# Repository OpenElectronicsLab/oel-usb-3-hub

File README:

Open Electronics Lab USB 3 hub
Copyright (C) 2022 Eric Herman
SPDX-License-Identifier: CERN-OHL-S-2.0+

This is a work in progress

License
-------
You may redistribute and modify this source and make products using it
under the terms of the CERN-OHL-S v2 (CERN Open Hardware Licence Version
2 - Strongly Reciprocal, https://ohwr.org/cern_ohl_s_v2.txt), or any
later version.

This source is distributed WITHOUT ANY EXPRESS OR IMPLIED WARRANTY,
INCLUDING OF MERCHANTABILITY, SATISFACTORY QUALITY AND FITNESS FOR A
PARTICULAR PURPOSE. Please see the CERN-OHL-S v2 for applicable
conditions.

Source location: https://github.com/OpenElectronicsLab/oel-usb-3-hub

As per CERN-OHL-S v2 section 4, should You produce hardware based on
this source, You must where practicable maintain the Source Location
visible on the external case of the Gizmo or other products you make
using this source.

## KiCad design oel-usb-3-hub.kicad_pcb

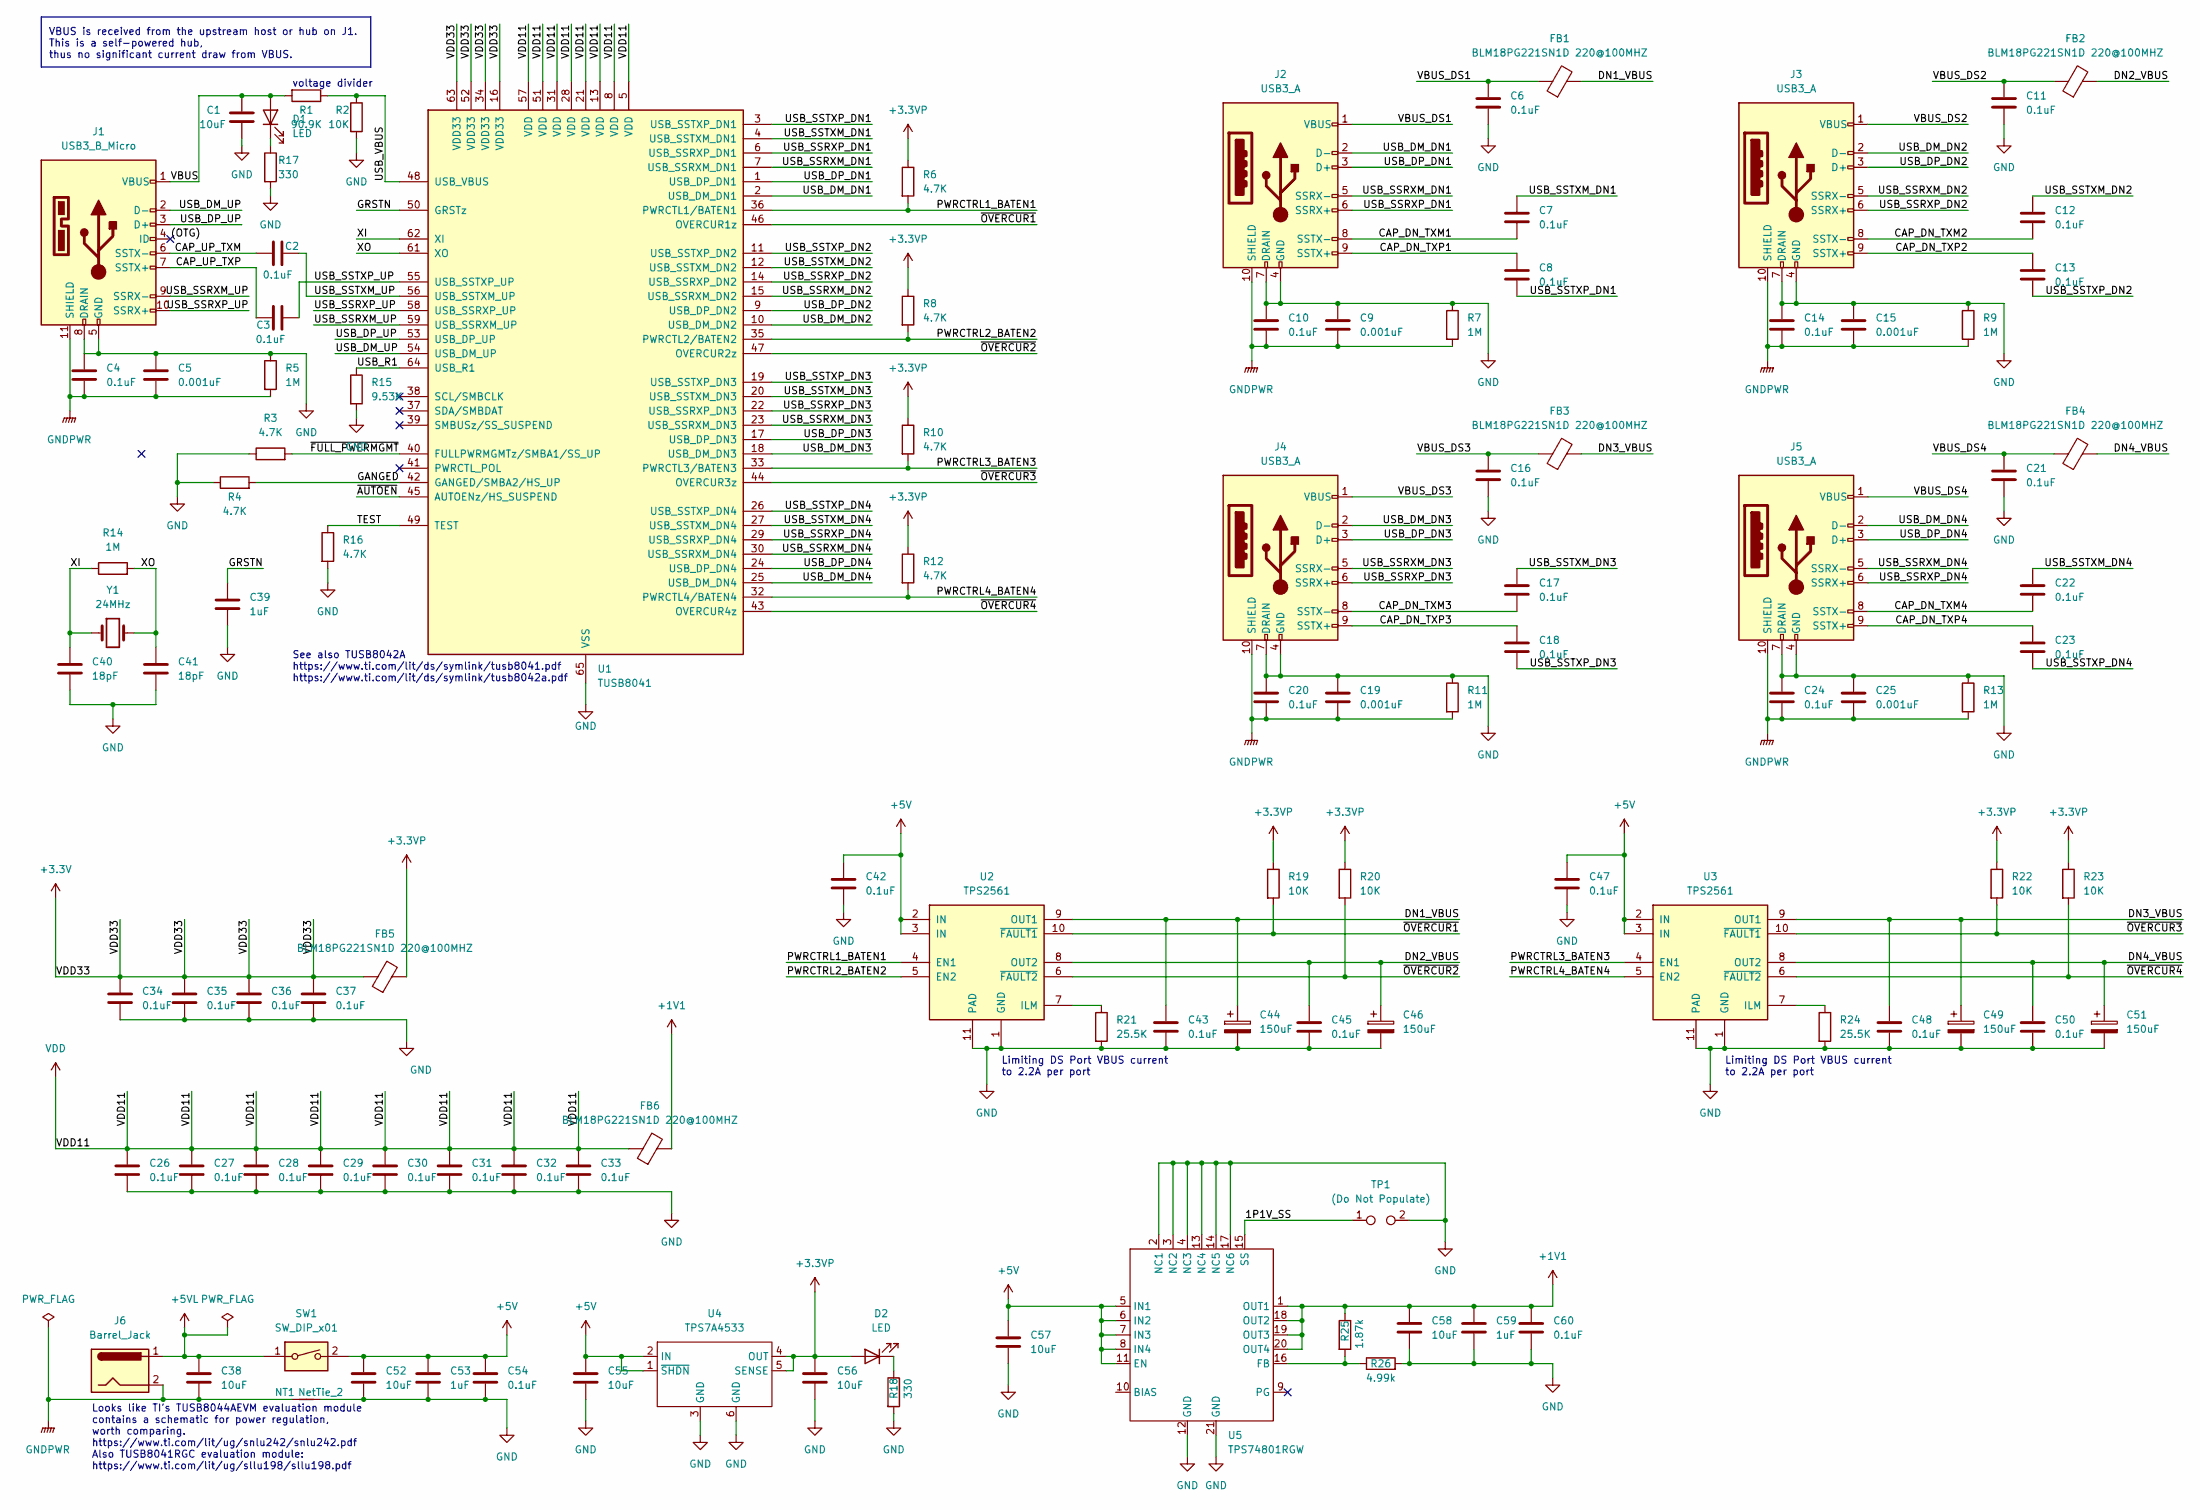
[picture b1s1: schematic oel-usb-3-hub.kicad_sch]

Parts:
C1, C38, C52, C55, C56, C57, C58: 10uF; C_0603_1608Metric_Pad1.08x0.95mm_HandSolder
C2, C3, C4, C6, C7, C8, C10, C11, C12, C13, C14, C16, C17, C18, C20, C21, C22, C23, C24, C26, C27, C28, C29, C30, C31, C32, C33, C34, C35, C36, C37, C42, C43, C45, C47, C48, C50, C54, C60: 0.1uF; C_0603_1608Metric_Pad1.08x0.95mm_HandSolder
C5, C9, C15, C19, C25: 0.001uF; C_0603_1608Metric_Pad1.08x0.95mm_HandSolder
C39, C53, C59: 1uF; C_0603_1608Metric_Pad1.08x0.95mm_HandSolder
C40, C41: 18pF; C_0603_1608Metric_Pad1.08x0.95mm_HandSolder
C44, C46, C49, C51: 150uF; C_0603_1608Metric_Pad1.08x0.95mm_HandSolder
D1, D2: LED; D_0603_1608Metric_Pad1.05x0.95mm_HandSolder
FB1, FB2, FB3, FB4, FB5, FB6: BLM18PG221SN1D 220@100MHZ; R_0603_1608Metric_Pad0.98x0.95mm_HandSolder
J1: USB3_B_Micro; USB3_Micro-B_Connfly_DS1104-01
J2, J3, J4, J5: USB3_A; USB3_A_Molex_48393-001
J6: Barrel_Jack; BarrelJack_Horizontal
NT1: NetTie_2; NetTie-2_SMD_Pad2.0mm
R1: 90.9K; R_0603_1608Metric_Pad0.98x0.95mm_HandSolder
R2, R19, R20, R22, R23: 10K; R_0603_1608Metric_Pad0.98x0.95mm_HandSolder
R3, R4, R6, R8, R10, R12, R16: 4.7K; R_0603_1608Metric_Pad0.98x0.95mm_HandSolder
R5, R7, R9, R11, R13, R14: 1M; R_0603_1608Metric_Pad0.98x0.95mm_HandSolder
R15: 9.53K; R_0603_1608Metric_Pad0.98x0.95mm_HandSolder
R17, R18: 330; R_0603_1608Metric_Pad0.98x0.95mm_HandSolder
R21, R24: 25.5K; R_0603_1608Metric_Pad0.98x0.95mm_HandSolder
R25: 1.87k; R_0603_1608Metric_Pad0.98x0.95mm_HandSolder
R26: 4.99k; R_0603_1608Metric_Pad0.98x0.95mm_HandSolder
SW1: SW_DIP_x01; SW_DIP_SPSTx01_Slide_6.7x4.1mm_W7.62mm_P2.54mm_LowProfile
TP1: (Do Not Populate); R_0603_1608Metric_Pad0.98x0.95mm_HandSolder
U1: TUSB8041; QFN-64-1EP_9x9mm_P0.5mm_EP6x6mm_ThermalVias
U2, U3: TPS2561; VSON-10-1EP_3x3mm_P0.5mm_EP1.65x2.4mm_ThermalVias
U4: TPS7A4533; SOT-223-6_TabPin3
U5: TPS74801RGW; Texas_S-PVQFN-N20_EP3.15x3.15mm_ThermalVias
Y1: 24MHz; Crystal_HC49-U_Vertical

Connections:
+1V1: C58.1, C59.1, C60.1, FB6.2, R25.1, U5.1 (OUT1), U5.18 (OUT2), U5.19 (OUT3), U5.20 (OUT4)
+3.3V: C34.1, C35.1, C36.1, C37.1, FB5.1, U1.16 (VDD33), U1.34 (VDD33), U1.52 (VDD33), U1.63 (VDD33)
+3.3VP: C56.1, D2.2 (A), FB5.2, R6.1, R8.1, R10.1, R12.1, R19.1, R20.1, R22.1, R23.1, U4.4 (OUT), U4.5 (SENSE)
+5V: C42.1, C47.1, C52.1, C53.1, C54.1, C55.1, C57.1, SW1.2, U2.2 (IN), U2.3 (IN), U3.2 (IN), U3.3 (IN), U4.1 (~SHDN), U4.2 (IN), U5.5 (IN1), U5.6 (IN2), U5.7 (IN3), U5.8 (IN4), U5.11 (EN)
+5VL: C38.1, J6.1, SW1.1
/1P1V_SS: TP1.1, U5.15 (SS)
/(OTG): J1.4 (ID)
/CAP_DN_TXM1: C7.2, J2.8 (SSTX-)
/CAP_DN_TXM2: C12.2, J3.8 (SSTX-)
/CAP_DN_TXM3: C17.2, J4.8 (SSTX-)
/CAP_DN_TXM4: C22.2, J5.8 (SSTX-)
/CAP_DN_TXP1: C8.1, J2.9 (SSTX+)
/CAP_DN_TXP2: C13.1, J3.9 (SSTX+)
/CAP_DN_TXP3: C18.1, J4.9 (SSTX+)
/CAP_DN_TXP4: C23.1, J5.9 (SSTX+)
/CAP_UP_TXM: C2.1, J1.6 (SSTX-)
/CAP_UP_TXP: C3.1, J1.7 (SSTX+)
/DN1_VBUS: C43.1, C44.1, FB1.2, U2.9 (OUT1)
/DN2_VBUS: C45.1, C46.1, FB2.2, U2.8 (OUT2)
/DN3_VBUS: C48.1, C49.1, FB3.2, U3.9 (OUT1)
/DN4_VBUS: C50.1, C51.1, FB4.2, U3.8 (OUT2)
/GANGED: R4.2, U1.42 (GANGED/SMBA2/HS_UP)
/GRSTN: C39.1, U1.50 (GRSTz)
/PWRCTRL1_BATEN1: R6.2, U1.36 (PWRCTL1/BATEN1), U2.4 (EN1)
/PWRCTRL2_BATEN2: R8.2, U1.35 (PWRCTL2/BATEN2), U2.5 (EN2)
/PWRCTRL3_BATEN3: R10.2, U1.33 (PWRCTL3/BATEN3), U3.4 (EN1)
/PWRCTRL4_BATEN4: R12.2, U1.32 (PWRCTL4/BATEN4), U3.5 (EN2)
/TEST: R16.1, U1.49 (TEST)
/USB_DM_DN1: J2.2 (D-), U1.2 (USB_DM_DN1)
/USB_DM_DN2: J3.2 (D-), U1.10 (USB_DM_DN2)
/USB_DM_DN3: J4.2 (D-), U1.18 (USB_DM_DN3)
/USB_DM_DN4: J5.2 (D-), U1.25 (USB_DM_DN4)
/USB_DM_UP: J1.2 (D-), U1.54 (USB_DM_UP)
/USB_DP_DN1: J2.3 (D+), U1.1 (USB_DP_DN1)
/USB_DP_DN2: J3.3 (D+), U1.9 (USB_DP_DN2)
/USB_DP_DN3: J4.3 (D+), U1.17 (USB_DP_DN3)
/USB_DP_DN4: J5.3 (D+), U1.24 (USB_DP_DN4)
/USB_DP_UP: J1.3 (D+), U1.53 (USB_DP_UP)
/USB_R1: R15.1, U1.64 (USB_R1)
/USB_SSRXM_DN1: J2.5 (SSRX-), U1.7 (USB_SSRXM_DN1)
/USB_SSRXM_DN2: J3.5 (SSRX-), U1.15 (USB_SSRXM_DN2)
/USB_SSRXM_DN3: J4.5 (SSRX-), U1.23 (USB_SSRXM_DN3)
/USB_SSRXM_DN4: J5.5 (SSRX-), U1.30 (USB_SSRXM_DN4)
/USB_SSRXM_UP: J1.9 (SSRX-), U1.59 (USB_SSRXM_UP)
/USB_SSRXP_DN1: J2.6 (SSRX+), U1.6 (USB_SSRXP_DN1)
/USB_SSRXP_DN2: J3.6 (SSRX+), U1.14 (USB_SSRXP_DN2)
/USB_SSRXP_DN3: J4.6 (SSRX+), U1.22 (USB_SSRXP_DN3)
/USB_SSRXP_DN4: J5.6 (SSRX+), U1.29 (USB_SSRXP_DN4)
/USB_SSRXP_UP: J1.10 (SSRX+), U1.58 (USB_SSRXP_UP)
/USB_SSTXM_DN1: C7.1, U1.4 (USB_SSTXM_DN1)
/USB_SSTXM_DN2: C12.1, U1.12 (USB_SSTXM_DN2)
/USB_SSTXM_DN3: C17.1, U1.20 (USB_SSTXM_DN3)
/USB_SSTXM_DN4: C22.1, U1.27 (USB_SSTXM_DN4)
/USB_SSTXM_UP: C2.2, U1.56 (USB_SSTXM_UP)
/USB_SSTXP_DN1: C8.2, U1.3 (USB_SSTXP_DN1)
/USB_SSTXP_DN2: C13.2, U1.11 (USB_SSTXP_DN2)
/USB_SSTXP_DN3: C18.2, U1.19 (USB_SSTXP_DN3)
/USB_SSTXP_DN4: C23.2, U1.26 (USB_SSTXP_DN4)
/USB_SSTXP_UP: C3.2, U1.55 (USB_SSTXP_UP)
/USB_VBUS: R1.1, R2.1, U1.48 (USB_VBUS)
/VBUS: C1.1, D1.2 (A), J1.1 (VBUS), R1.2
/VBUS_DS1: C6.1, FB1.1, J2.1 (VBUS)
/VBUS_DS2: C11.1, FB2.1, J3.1 (VBUS)
/VBUS_DS3: C16.1, FB3.1, J4.1 (VBUS)
/VBUS_DS4: C21.1, FB4.1, J5.1 (VBUS)
/XI: C40.1, R14.1, U1.62 (XI), Y1.1
/XO: C41.2, R14.2, U1.61 (XO), Y1.2
/~AUTOEN: U1.45 (AUTOENz/HS_SUSPEND)
/~FULL_PWERMGMT: R3.2, U1.40 (FULLPWRMGMTz/SMBA1/SS_UP)
/~OVERCUR1: R19.2, U1.46 (OVERCUR1z), U2.10 (~FAULT1)
/~OVERCUR2: R20.2, U1.47 (OVERCUR2z), U2.6 (~FAULT2)
/~OVERCUR3: R22.2, U1.44 (OVERCUR3z), U3.10 (~FAULT1)
/~OVERCUR4: R23.2, U1.43 (OVERCUR4z), U3.6 (~FAULT2)
GND: C1.2, C4.1, C5.1, C6.2, C9.1, C10.1, C11.2, C14.1, C15.1, C16.2, C19.1, C20.1, C21.2, C24.1, C25.1, C26.2, C27.2, C28.2, C29.2, C30.2, C31.2, C32.2, C33.2, C34.2, C35.2, C36.2, C37.2, C39.2, C40.2, C41.1, C42.2, C43.2, C44.2, C45.2, C46.2, C47.2, C48.2, C49.2, C50.2, C51.2, C52.2, C53.2, C54.2, C55.2, C56.2, C57.2, C58.2, C59.2, C60.2, J1.5 (GND), J1.8 (DRAIN), J2.4 (GND), J2.7 (DRAIN), J3.4 (GND), J3.7 (DRAIN), J4.4 (GND), J4.7 (DRAIN), J5.4 (GND), J5.7 (DRAIN), NT1.2, R2.2, R3.1, R4.1, R5.1, R7.1, R9.1, R11.1, R13.1, R15.2, R16.2, R17.2, R18.2, R21.2, R24.2, R26.2, TP1.2, U1.65 (VSS), U2.1 (GND), U2.11 (PAD), U3.1 (GND), U3.11 (PAD), U4.3 (GND), U4.6 (GND), U5.2 (NC1), U5.3 (NC2), U5.4 (NC3), U5.12 (GND), U5.13 (NC4), U5.14 (NC5), U5.17 (NC6), U5.21 (GND)
GNDPWR: C4.2, C5.2, C9.2, C10.2, C14.2, C15.2, C19.2, C20.2, C24.2, C25.2, C38.2, J1.11 (SHIELD), J2.10 (SHIELD), J3.10 (SHIELD), J4.10 (SHIELD), J5.10 (SHIELD), J6.2, NT1.1, R5.2, R7.2, R9.2, R11.2, R13.2
unnamed: D1.1 (K), R17.1
unnamed: D2.1 (K), R18.1
unnamed: R21.1, U2.7 (ILM)
unnamed: R24.1, U3.7 (ILM)
unnamed: R25.2, R26.1, U5.16 (FB)
VDD: C26.1, C27.1, C28.1, C29.1, C30.1, C31.1, C32.1, C33.1, FB6.1, U1.5 (VDD), U1.8 (VDD), U1.13 (VDD), U1.21 (VDD), U1.28 (VDD), U1.31 (VDD), U1.51 (VDD), U1.57 (VDD)

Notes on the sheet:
See also TUSB8042A https://www.ti.com/lit/ds/symlink/tusb8041.pdf https://www.ti.com/lit/ds/symlink/tusb8042a.pdf
voltage divider
Limiting DS Port VBUS current to 2.2A per port
Looks like TI's TUSB8044AEVM evaluation module contains a schematic for power regulation, worth comparing. https://www.ti.com/lit/ug/snlu242/snlu242.pdf Also TUSB8041RGC evaluation module: https://www.ti.com/lit/ug/sllu198/sllu198.pdf
VBUS is received from the upstream host or hub on J1. This is a self-powered hub, thus no significant current draw from VBUS.

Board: 2 copper layers, 109 parts (0 on the bottom side), 79 nets, no tracks yet.

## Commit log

2022-06-26 init
2022-06-26 SPDX-License-Identifier: CERN-OHL-S-2.0+
2022-08-30 Add power to schematic
2022-08-30 First sketch of PCB layout
    Looks like some pieces may need to be mounted to the bottom of the PCB.
